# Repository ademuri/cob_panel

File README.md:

# cob_panel

This is a collection of designs for PCBs for the Colordance Circle project.

This is not an official Google open-source project.

## cob_2x2

`cob_2x2` is a 2x2 high-power RGB LED board. It uses the common WS2811 chip to control four "9W" RGB LEDs. These are the 700mA, 6-pin RGB LEDs found on Aliexpress et al. I'm using [these](https://www.aliexpress.com/item/32950854541.html?spm=a2g0s.9042311.0.0.17f04c4dzGsUTR), the "6Pin 9W RGB" version. These LEDs are controlled via the standard WS2812 one-wire protocol. The boards can be tiled into a 2x2 grid of boards, yielding a 4x4 grid of LEDs. The board-edge headers transmit power and signal. The boards also have an on-board Anderson PowerPole connector for 12v power, and a 1x02 header for LED signal in. An onboard jumper is used to control whether the LED signal is also chained through the board-edge header.

The pitch between LEDs is 80mm.

Note: this board is as-yet untested.

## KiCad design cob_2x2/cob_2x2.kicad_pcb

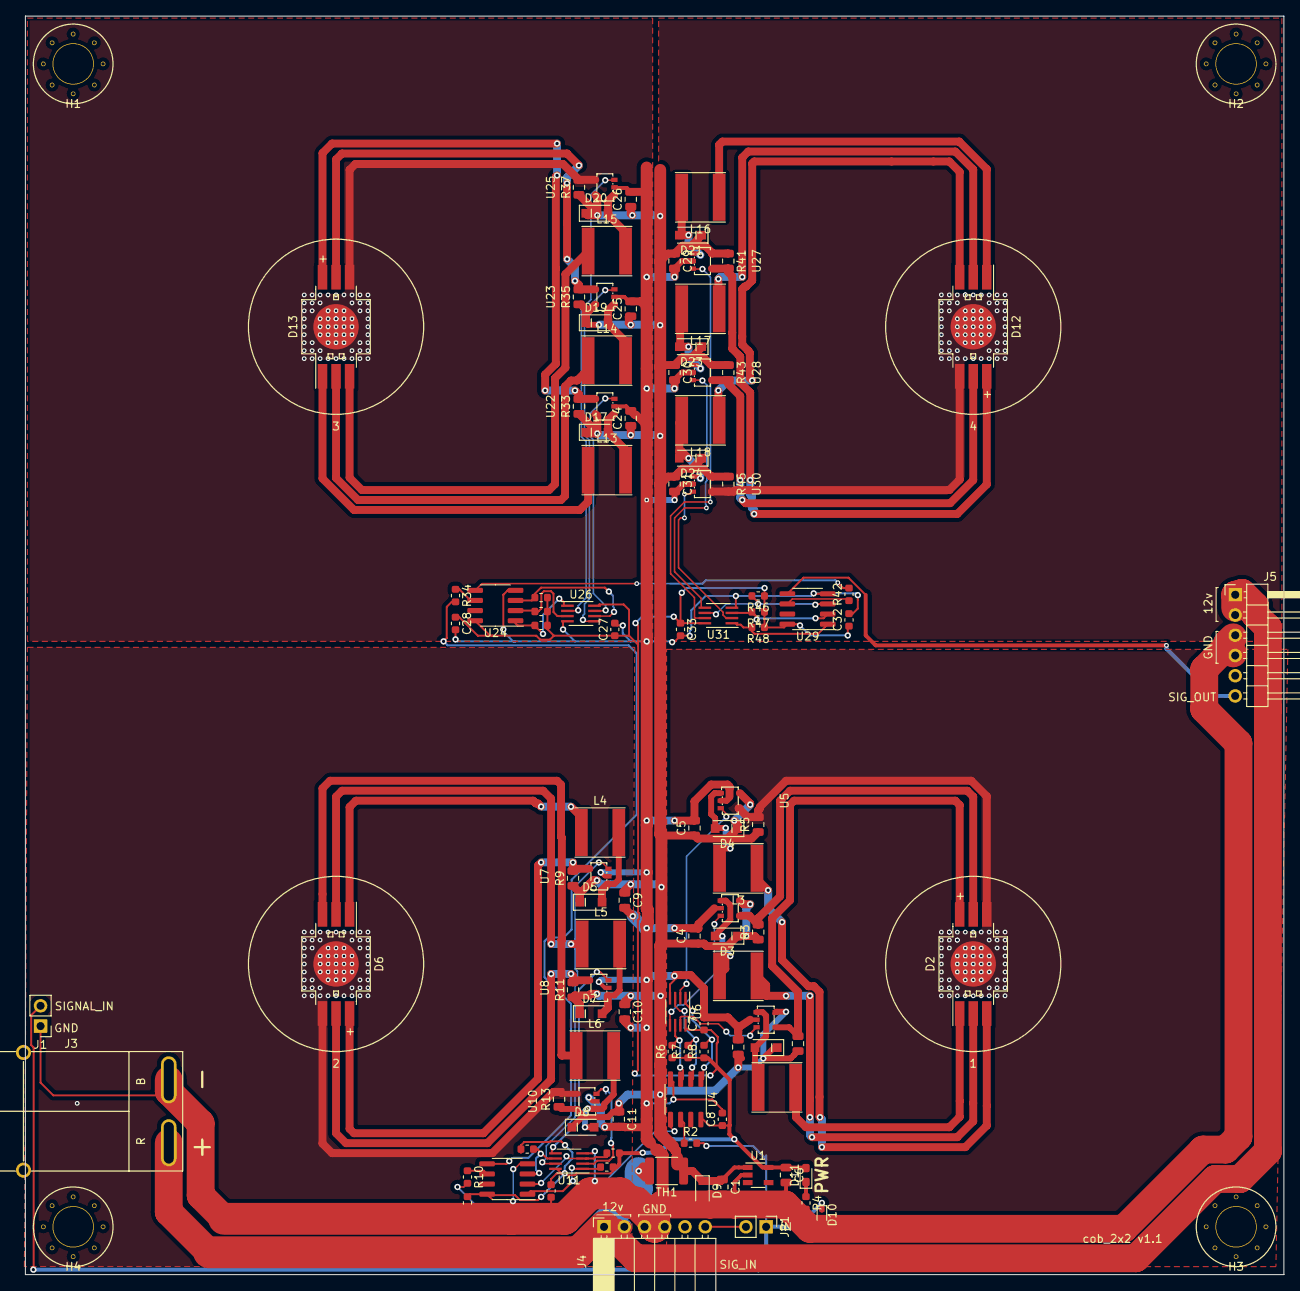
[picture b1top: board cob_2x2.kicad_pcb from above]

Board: 2 copper layers, 158.0 x 158.0 mm, 113 parts (0 on the bottom side), 75 nets.

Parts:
C1, C3, C4, C5, C6, C9, C10, C11, C24, C25, C26, C29, C30, C31: 10uF; C_0805_2012Metric
C7, C8, C12, C13, C27, C28, C32, C33: .1uF; C_0603_1608Metric
D1, D3, D4, D5, D7, D8, D17, D19, D20, D21, D23, D24: D_Schottky; D_SOD-123F
D2, D6, D12, D13: LED_RGB; LED_RGB_EPISTAR_6PIN_RGB
D9: D_TVS_12V; D_SOD-323_HandSoldering
D10: D_TVS_5V; D_SOD-523
D11: LED; LED_0603_1608Metric_Pad1.05x0.95mm_HandSolder
H1, H2, H3, H4: MountingHole; HOLE_5MM_#8
J1: Conn_01x02; PinHeader_1x02_P2.54mm_Vertical
J3: Anderson_two_redblack; Anderson_1337G3_right_angle_bottom_two
J4: Conn_01x06_Female; PinSocket_1x06_P2.54mm_Horizontal
J5: Conn_01x06_Male; PinHeader_1x06_P2.54mm_Horizontal
JP1: Jumper; PinHeader_1x02_P2.54mm_Vertical
L1, L2, L3, L4, L5, L6, L13, L14, L15, L16, L17, L18: 47uH; L_Taiyo-Yuden_NR-60xx
R1, R3, R5, R9, R11, R13, R33, R35, R37, R41, R43, R45: .143; R_0805_2012Metric
R2, R10, R34, R42: 33; R_0603_1608Metric
R4: 6k8; R_0603_1608Metric
R6, R7, R8, R14, R15, R16, R38, R39, R40, R46, R47, R48: 10k; R_0603_1608Metric
TH1: Thermistor_PTC; R_1812_4532Metric
U1: 5V_REG_AP7370-50W5-7; TSOT-23-5
U2, U3, U5, U7, U8, U10, U22, U23, U25, U27, U28, U30: AL8860_LED_DRIVER; SOT-25
U4, U9, U24, U29: WS2811; SOP-8_3.76x4.96mm_P1.27mm
U6, U11, U26, U31: 3_Inverter_TC7WH14FU,LJ(CT; SSOP-8_2.95x2.8mm_P0.65mm

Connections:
12V_RAW: J3.1, J4.1, J4.2, J5.1, J5.2, TH1.2
+5V: C6.1, C7.1, C8.1, C12.1, C13.1, C27.1, C28.1, C32.1, C33.1, D11.2, R6.1, R7.1, R8.1, R14.1, R15.1, R16.1, R38.1, R39.1, R40.1, R46.1, R47.1, R48.1, U1.5, U4.8, U6.8, U9.8, U11.8, U24.8, U26.8, U29.8, U31.8
+12V: C1.1, C3.1, C4.1, C5.1, C9.1, C10.1, C11.1, C24.1, C25.1, C26.1, C29.1, C30.1, C31.1, D1.1, D3.1, D4.1, D5.1, D7.1, D8.1, D9.1, D17.1, D19.1, D20.1, D21.1, D23.1, D24.1, R1.1, R3.1, R5.1, R9.1, R11.1, R13.1, R33.1, R35.1, R37.1, R41.1, R43.1, R45.1, TH1.1, U1.1, U2.5, U3.5, U5.5, U7.5, U8.5, U10.5, U22.5, U23.5, U25.5, U27.5, U28.5, U30.5
/sheet5DF1A510/B_INVERTED: R38.2, U24.3, U26.6
/sheet5DF1A510/B_LED_A: D13.4, R37.2, U25.4
/sheet5DF1A510/B_LED_K: D13.3, L15.1
/sheet5DF1A510/B_SIGNAL: U25.3, U26.2
/sheet5DF1A510/G_INVERTED: R39.2, U24.2, U26.3
/sheet5DF1A510/G_LED_A: D13.5, R35.2, U23.4
/sheet5DF1A510/G_LED_K: D13.2, L14.1
/sheet5DF1A510/G_SIGNAL: U23.3, U26.5
/sheet5DF1A510/R_INVERTED: R40.2, U24.1, U26.1
/sheet5DF1A510/R_LED_A: D13.6, R33.2, U22.4
/sheet5DF1A510/R_LED_K: D13.1, L13.1
/sheet5DF1A510/R_SIGNAL: U22.3, U26.7
/sheet5DF1A510/SIGNAL_IN: R34.2, U9.5
/sheet5DF1FB98/B_INVERTED: R46.2, U29.3, U31.6
/sheet5DF1FB98/B_LED_A: D12.4, R45.2, U30.4
/sheet5DF1FB98/B_LED_K: D12.3, L18.1
/sheet5DF1FB98/B_SIGNAL: U30.3, U31.2
/sheet5DF1FB98/G_INVERTED: R47.2, U29.2, U31.3
/sheet5DF1FB98/G_LED_A: D12.5, R43.2, U28.4
/sheet5DF1FB98/G_LED_K: D12.2, L17.1
/sheet5DF1FB98/G_SIGNAL: U28.3, U31.5
/sheet5DF1FB98/R_INVERTED: R48.2, U29.1, U31.1
/sheet5DF1FB98/R_LED_A: D12.6, R41.2, U27.4
/sheet5DF1FB98/R_LED_K: D12.1, L16.1
/sheet5DF1FB98/R_SIGNAL: U27.3, U31.7
/sheet5DF1FB98/SIGNAL_IN: R42.2, U24.5
/sheet5DF187B4/B_INVERTED: R14.2, U9.3, U11.6
/sheet5DF187B4/B_LED_A: D6.4, R13.2, U10.4
/sheet5DF187B4/B_LED_K: D6.3, L6.1
/sheet5DF187B4/B_SIGNAL: U10.3, U11.2
/sheet5DF187B4/G_INVERTED: R15.2, U9.2, U11.3
/sheet5DF187B4/G_LED_A: D6.5, R11.2, U8.4
/sheet5DF187B4/G_LED_K: D6.2, L5.1
/sheet5DF187B4/G_SIGNAL: U8.3, U11.5
/sheet5DF187B4/R_INVERTED: R16.2, U9.1, U11.1
/sheet5DF187B4/R_LED_A: D6.6, R9.2, U7.4
/sheet5DF187B4/R_LED_K: D6.1, L4.1
/sheet5DF187B4/R_SIGNAL: U7.3, U11.7
/sheet5DF187B4/SIGNAL_IN: R10.2, U4.5
/single_led/B_INVERTED: R6.2, U4.3, U6.6
/single_led/B_LED_A: D2.4, R5.2, U5.4
/single_led/B_LED_K: D2.3, L3.1
/single_led/B_SIGNAL: U5.3, U6.2
/single_led/G_INVERTED: R7.2, U4.2, U6.3
/single_led/G_LED_A: D2.5, R3.2, U3.4
/single_led/G_LED_K: D2.2, L2.1
/single_led/G_SIGNAL: U3.3, U6.5
/single_led/R_INVERTED: R8.2, U4.1, U6.1
/single_led/R_LED_A: D2.6, R1.2, U2.4
/single_led/R_LED_K: D2.1, L1.1
/single_led/R_SIGNAL: U2.3, U6.7
GND: C1.2, C3.2, C4.2, C5.2, C6.2, C7.2, C8.2, C9.2, C10.2, C11.2, C12.2, C13.2, C24.2, C25.2, C26.2, C27.2, C28.2, C29.2, C30.2, C31.2, C32.2, C33.2, D9.2, D10.2, J1.1, J3.2, J4.3, J4.4, J5.3, J5.4, R4.2, U1.2, U2.2, U3.2, U4.4, U5.2, U6.4, U7.2, U8.2, U9.4, U10.2, U11.4, U22.2, U23.2, U24.4, U25.2, U26.4, U27.2, U28.2, U29.4, U30.2, U31.4
unnamed: D1.2, L1.2, U2.1
unnamed: D3.2, L2.2, U3.1
unnamed: D4.2, L3.2, U5.1
unnamed: D5.2, L4.2, U7.1
unnamed: D7.2, L5.2, U8.1
unnamed: D8.2, L6.2, U10.1
unnamed: D11.1, R4.1
unnamed: D17.2, L13.2, U22.1
unnamed: D19.2, L14.2, U23.1
unnamed: D20.2, L15.2, U25.1
unnamed: D21.2, L16.2, U27.1
unnamed: D23.2, L17.2, U28.1
unnamed: D24.2, L18.2, U30.1
unnamed: J4.6, JP1.2
unnamed: R2.1, U4.6
unnamed: R10.1, U9.6
unnamed: R34.1, U24.6
unnamed: R42.1, U29.6
SIGNAL_IN: D10.1, J1.2, JP1.1, R2.2
SIGNAL_OUT: J5.6, U29.5

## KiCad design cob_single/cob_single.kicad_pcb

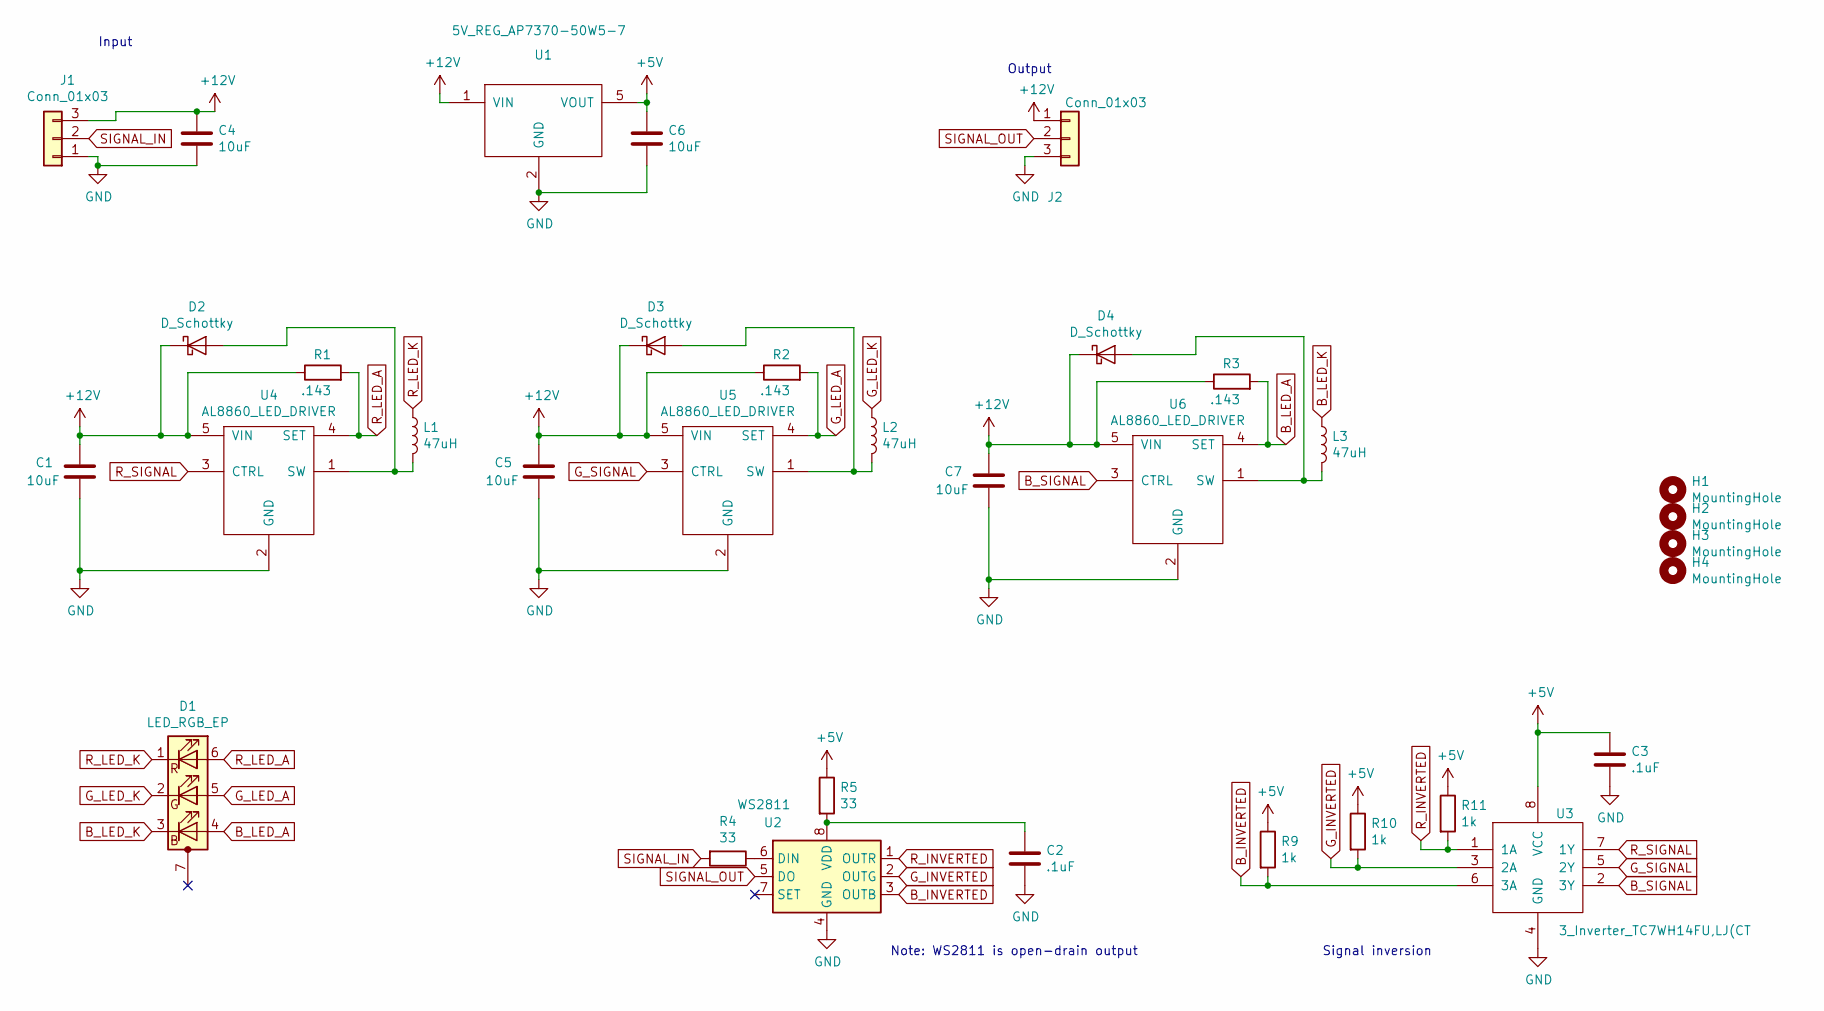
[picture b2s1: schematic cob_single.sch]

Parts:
C1, C4, C5, C6, C7: 10uF; C_0805_2012Metric
C2, C3: .1uF; C_0603_1608Metric
D1: LED_RGB_EP; LED_RGB_EPISTAR_6PIN_RGB
D2, D3, D4: D_Schottky; D_SOD-123F
H1, H2, H3, H4: MountingHole; MountingHole_2.7mm_M2.5
J1, J2: Conn_01x03; PinHeader_1x03_P2.54mm_Vertical
L1, L2, L3: 47uH; L_Taiyo-Yuden_NR-60xx
R1, R2, R3: .143; R_0805_2012Metric
R4, R5: 33; R_0603_1608Metric
R9, R10, R11: 1k; R_0603_1608Metric
U1: 5V_REG_AP7370-50W5-7; TSOT-23-5
U2: WS2811; SOP-8_3.76x4.96mm_P1.27mm
U3: 3_Inverter_TC7WH14FU,LJ(CT; TSSOP-8_3x3mm_P0.65mm
U4, U5, U6: AL8860_LED_DRIVER; SOT-25

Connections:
+5V: C3.1, C6.1, R5.1, R9.1, R10.1, R11.1, U1.5 (VOUT), U3.8 (VCC)
+12V: C1.1, C4.1, C5.1, C7.1, D2.1 (K), D3.1 (K), D4.1 (K), J1.3, J2.1, R1.1, R2.1, R3.1, U1.1 (VIN), U4.5 (VIN), U5.5 (VIN), U6.5 (VIN)
B_INVERTED: R9.2, U2.3 (OUTB), U3.6 (3A)
B_LED_A: D1.4 (BA), R3.2, U6.4 (SET)
B_LED_K: D1.3 (BK), L3.1
B_SIGNAL: U3.2 (3Y), U6.3 (CTRL)
GND: C1.2, C2.2, C3.2, C4.2, C5.2, C6.2, C7.2, J1.1, J2.3, U1.2 (GND), U2.4 (GND), U3.4 (GND), U4.2 (GND), U5.2 (GND), U6.2 (GND)
G_INVERTED: R10.2, U2.2 (OUTG), U3.3 (2A)
G_LED_A: D1.5 (GA), R2.2, U5.4 (SET)
G_LED_K: D1.2 (GK), L2.1
G_SIGNAL: U3.5 (2Y), U5.3 (CTRL)
unnamed: C2.1, R5.2, U2.8 (VDD)
unnamed: D2.2 (A), L1.2, U4.1 (SW)
unnamed: D3.2 (A), L2.2, U5.1 (SW)
unnamed: D4.2 (A), L3.2, U6.1 (SW)
unnamed: R4.1, U2.6 (DIN)
R_INVERTED: R11.2, U2.1 (OUTR), U3.1 (1A)
R_LED_A: D1.6 (RA), R1.2, U4.4 (SET)
R_LED_K: D1.1 (RK), L1.1
R_SIGNAL: U3.7 (1Y), U4.3 (CTRL)
SIGNAL_IN: J1.2, R4.2
SIGNAL_OUT: J2.2, U2.5 (DO)

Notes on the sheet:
Input
Signal inversion
Note: WS2811 is open-drain output
Output

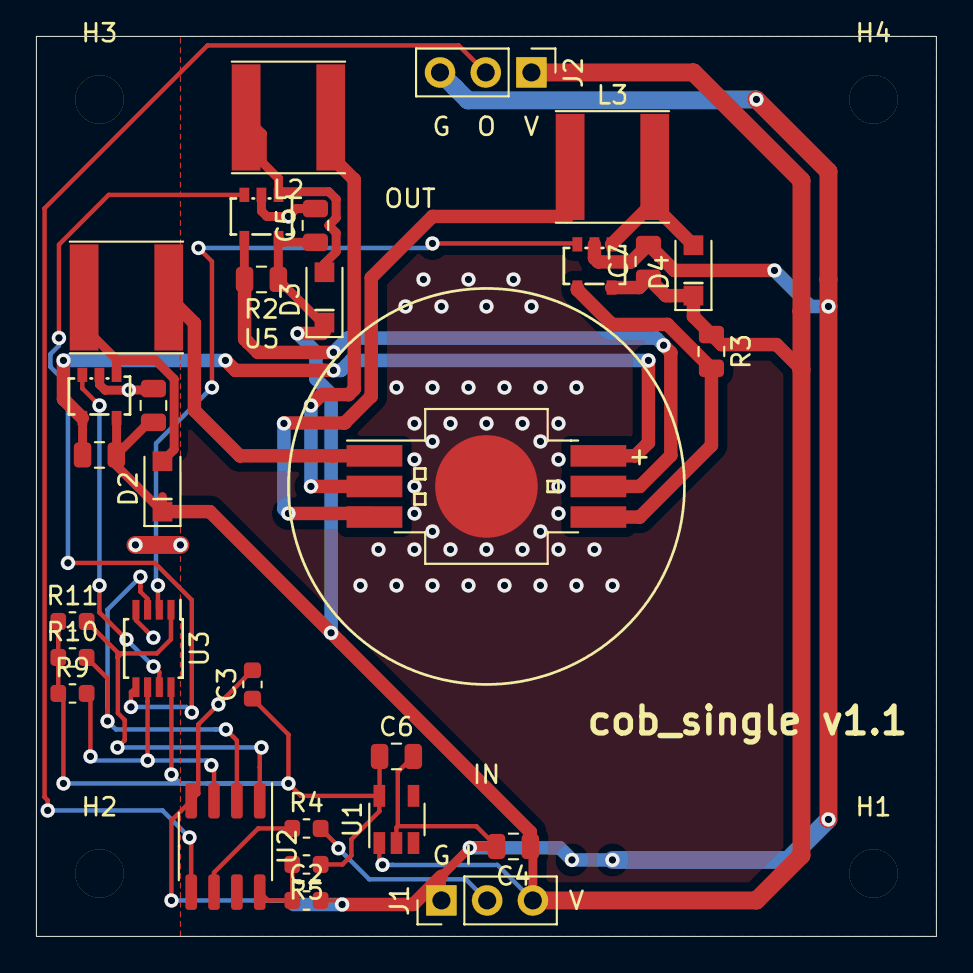
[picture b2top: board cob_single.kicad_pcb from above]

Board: 2 copper layers, 50.0 x 50.0 mm, 34 parts (0 on the bottom side), 22 nets.

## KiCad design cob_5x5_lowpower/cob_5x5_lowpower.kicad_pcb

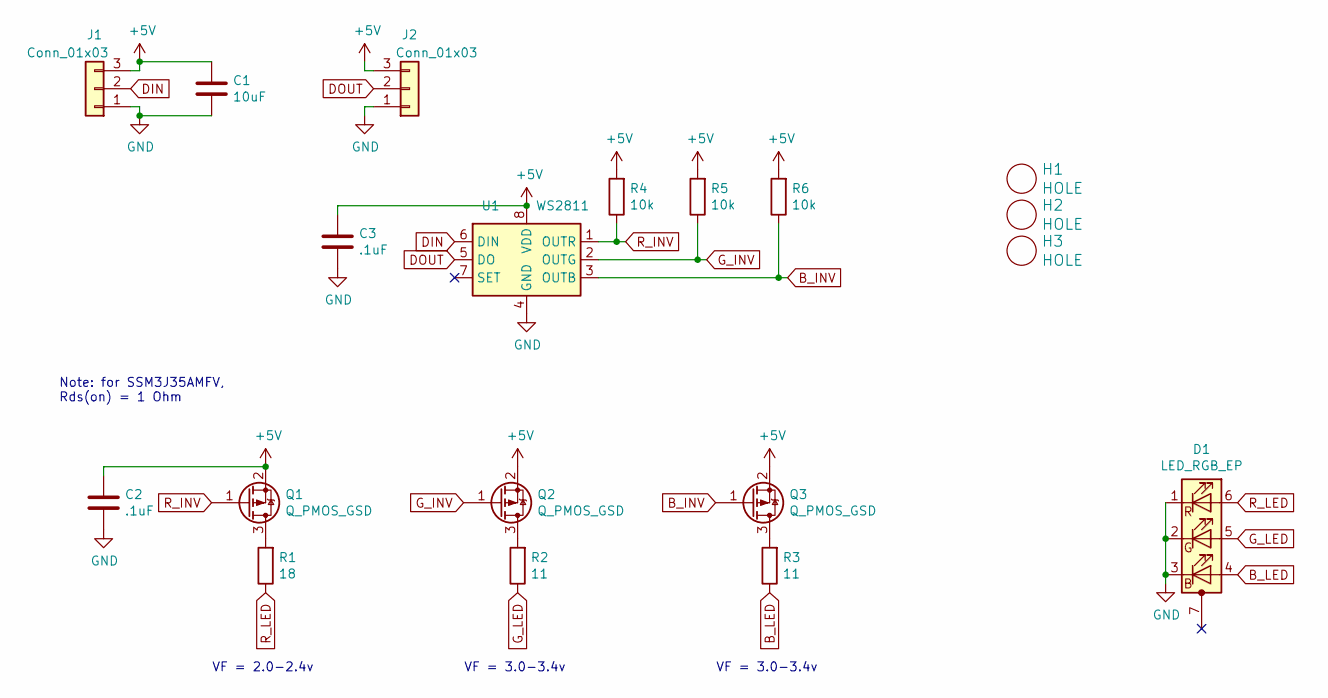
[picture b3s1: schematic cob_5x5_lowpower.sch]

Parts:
C1: 10uF; C_0805_2012Metric
C2, C3: .1uF; C_0603_1608Metric
D1: LED_RGB_EP; LED_RGB_EPISTAR_6PIN_RGB
H1, H2, H3: HOLE; MountingHole_2.7mm_M2.5
J1, J2: Conn_01x03; PinHeader_1x03_P2.54mm_Vertical
Q1, Q2, Q3: Q_PMOS_GSD; SOT-723
R1: 18; R_1210_3225Metric
R2, R3: 11; R_1210_3225Metric
R4, R5, R6: 10k; R_0603_1608Metric
U1: WS2811; SOP-8_3.76x4.96mm_P1.27mm

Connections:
+5V: C1.1, C2.1, C3.1, J1.3, J2.3, Q1.2 (S), Q2.2 (S), Q3.2 (S), R4.2, R5.2, R6.2, U1.8 (VDD)
B_INV: Q3.1 (G), R6.1, U1.3 (OUTB)
B_LED: D1.4 (BA), R3.1
DIN: J1.2, U1.6 (DIN)
DOUT: J2.2, U1.5 (DO)
GND: C1.2, C2.2, C3.2, D1.1 (RK), D1.2 (GK), D1.3 (BK), J1.1, J2.1, U1.4 (GND)
G_INV: Q2.1 (G), R5.1, U1.2 (OUTG)
G_LED: D1.5 (GA), R2.1
unnamed: Q1.3 (D), R1.2
unnamed: Q2.3 (D), R2.2
unnamed: Q3.3 (D), R3.2
R_INV: Q1.1 (G), R4.1, U1.1 (OUTR)
R_LED: D1.6 (RA), R1.1

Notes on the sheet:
Note: for SSM3J35AMFV, Rds(on) = 1 Ohm
VF = 2.0-2.4v
VF = 3.0-3.4v

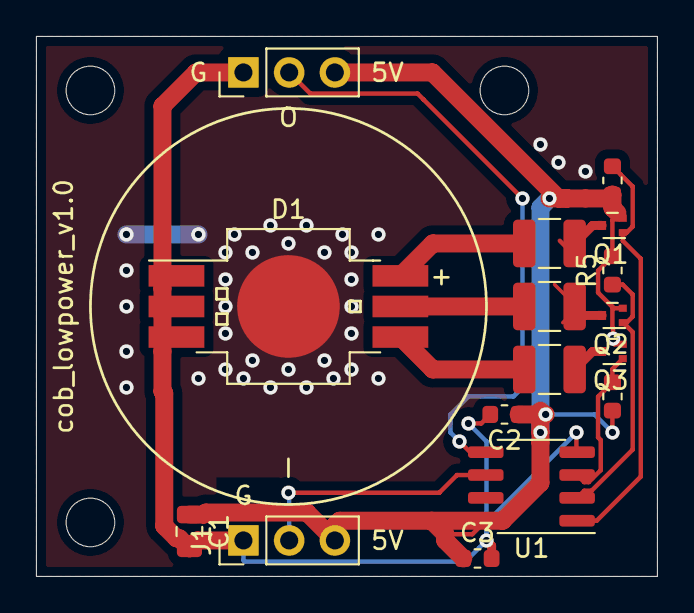
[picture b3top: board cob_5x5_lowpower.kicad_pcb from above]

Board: 2 copper layers, 34.5 x 30.0 mm, 19 parts (0 on the bottom side), 13 nets.

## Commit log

2019-10-26 WIP add mini panel
2019-10-26 WIP associate footprints
2019-10-26 WIP rev v1.0
2019-10-29 Revision 1.0 with linear driver
2019-10-31 Re-do revision 1.0 with 5V switching driver
2019-11-02 Convert v1.0 to 12v supply/12v tolerant switching driver.
2019-11-07 Add 5x5 low power cob board
2019-11-14 Add fab sheet for cob_single
2019-11-18 High-power revision 1.1:
    - Fixed LED thermal pad to not connect to ground
    - Fixed clearance for LED lens
    - Added orientation for diodes and LED
2019-11-18 Lowpower one-off revision 1.0.
    Updated previous attempt (unfabricated) with lessons from from
    high-power board.
2019-12-03 Add thermal notes
2019-12-03 Add cob_3x3, create schematic for it
2019-12-14 Add TVCs and power indicator to schematic.
2019-12-16 Schematic and footprints ready for v1.0:
    - Added board-to-board connectors for chaining a 2x2 array of 2x2
    boards.
2020-01-07 Hardware revision v1.0 complete
2020-01-07 Add license and readme
2020-02-23 cob_2x2 v1.1:
    - Fix inverter footprint
    - Increase size of 5V TVS diode to SOD-523
    - Increase clearance for mounting holes by 1mm
    - Make mounting holes evenly spaced
2020-03-08 Add Anderson connector 3d model
2021-06-14 Add HTML bom
